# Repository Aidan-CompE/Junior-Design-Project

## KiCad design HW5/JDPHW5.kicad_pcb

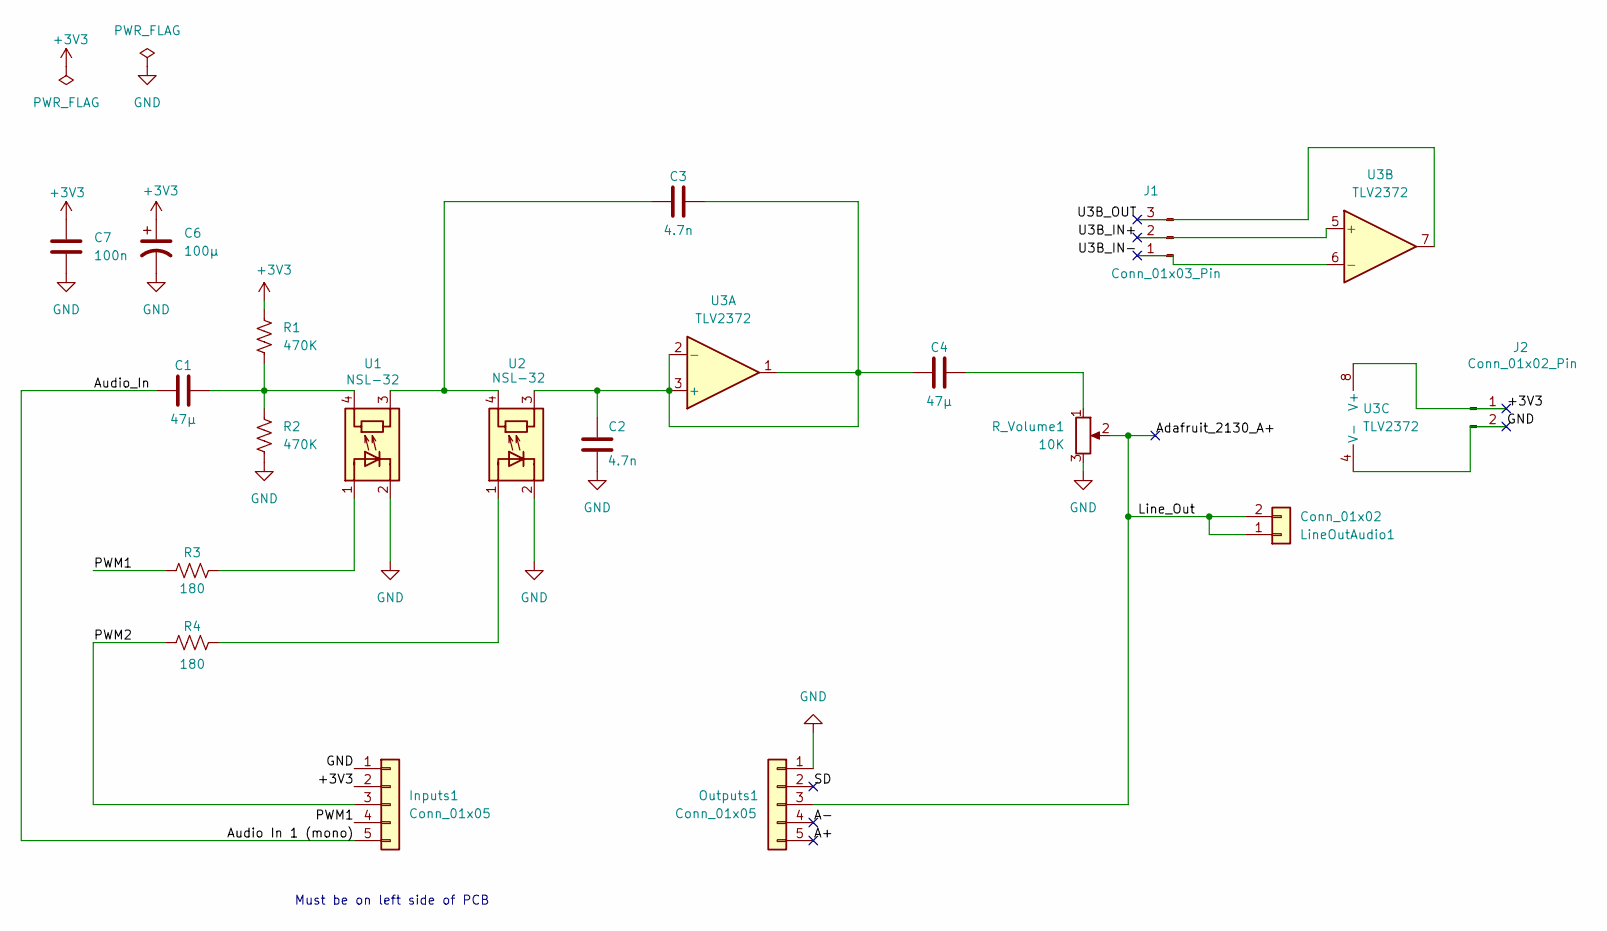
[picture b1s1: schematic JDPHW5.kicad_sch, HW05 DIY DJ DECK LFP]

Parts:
C1, C4: 47μ; C_Disc_D6.0mm_W4.4mm_P5.00mm
C2, C3: 4.7n; C_Disc_D4.7mm_W2.5mm_P5.00mm
C6: 100μ; C_Radial_D5.0mm_H11.0mm_P2.00mm
C7: 100n; C_Disc_D5.0mm_W2.5mm_P2.50mm
Inputs1: Conn_01x05; PinHeader_1x05_P2.54mm_Vertical
J1: Conn_01x03_Pin; PinHeader_1x03_P2.54mm_Vertical
J2: Conn_01x02_Pin; PinHeader_1x02_P2.54mm_Vertical
LineOutAudio1: Conn_01x02; PinHeader_1x02_P2.54mm_Vertical
Outputs1: Conn_01x05; PinHeader_1x05_P2.54mm_Vertical
R1, R2: 470K; R_Axial_DIN0207_L6.3mm_D2.5mm_P7.62mm_Horizontal
R3, R4: 180; R_Axial_DIN0207_L6.3mm_D2.5mm_P7.62mm_Horizontal
R_Volume1: 10K; Potentiometer_Bourns_PTV09A-1_Single_Vertical
U1, U2: NSL-32; Luna_NSL-32
U3: TLV2372; DIP-8_W7.62mm

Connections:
+3V3: C6.1, C7.1, Inputs1.2, J2.1, R1.1, U3.8 (V+)
/A+: Outputs1.5
/A-: Outputs1.4
/Adafruit_2130_A+: LineOutAudio1.1, LineOutAudio1.2, Outputs1.3, R_Volume1.2
/Audio In 1 (mono): C1.1, Inputs1.5
/PWM1: Inputs1.4, R3.1
/PWM2: Inputs1.3, R4.1
/SD: Outputs1.2
/U3B_IN+: J1.2, U3.5 (+)
/U3B_IN-: J1.1, U3.6 (-)
/U3B_OUT: J1.3, U3.7
GND: C2.2, C6.2, C7.2, Inputs1.1, J2.2, Outputs1.1, R2.2, R_Volume1.3, U1.2 (K), U2.2 (K), U3.4 (V-)
unnamed: C1.2, R1.2, R2.1, U1.4 (R)
unnamed: C3.1, U1.3 (R), U2.4 (R)
unnamed: C4.2, R_Volume1.1
unnamed: R3.2, U1.1 (A)
unnamed: R4.2, U2.1 (A)
unnamed: C2.1, C3.2, C4.1, U2.3 (R), U3.1, U3.2 (-), U3.3 (+)

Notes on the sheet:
Must be on left side of PCB

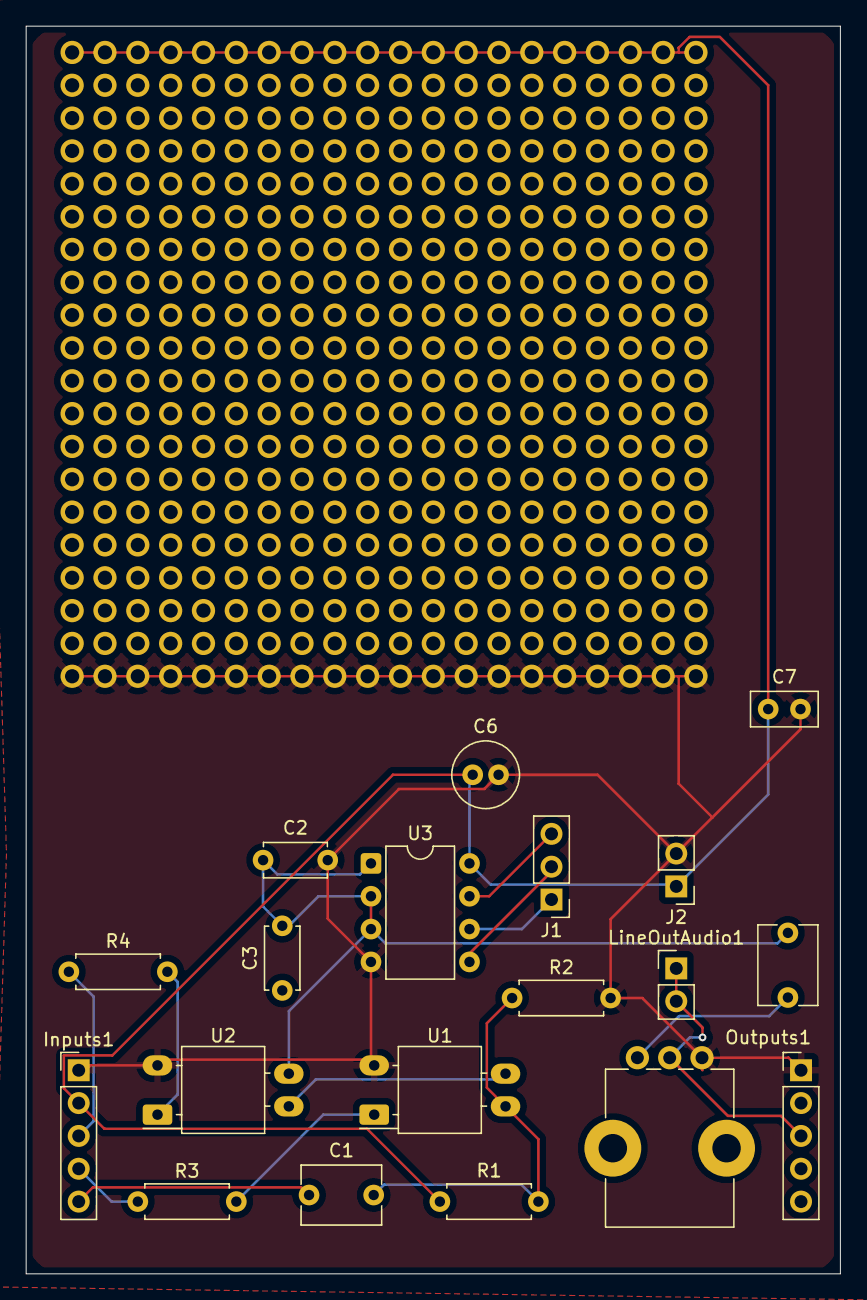
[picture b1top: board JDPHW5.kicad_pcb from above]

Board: 2 copper layers, 63.0 x 96.5 mm, 19 parts (0 on the bottom side), 15 nets.

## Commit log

2026-03-04 Most of Schematic Done
    Need to wire all op amp units to header pins and add AE9986-ND part
2026-03-04 Forgot to save
    saved
2026-03-05 Schematic Done
    Should be done now with schematic
2026-03-10 Final
2026-03-12 Quicksave
2026-03-12 Save
    Some things still need footprints like the pins but mostly just need to connect things now I believe
2026-03-13 PCB and Sch
    Files done
2026-03-13 Rename
2026-03-14 Gerbers added
2026-03-14 Comit before submit
